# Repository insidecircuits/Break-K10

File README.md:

Break-K10
=========

Breakout board for Freescale Kinetis K10 QFN package - single sided PCB
![screenshot] (board scr.PNG)

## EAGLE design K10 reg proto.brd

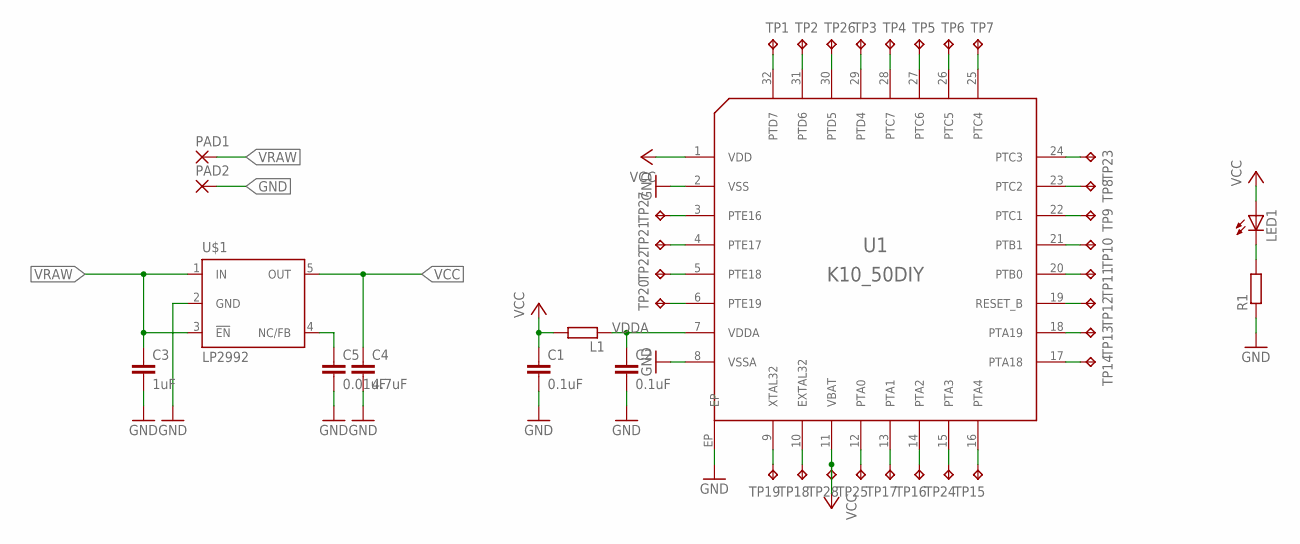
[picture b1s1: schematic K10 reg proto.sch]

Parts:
C1, C2: 0.1uF; C0805
C3: 1uF; C0805
C4: 4.7uF; C0805
C5: 0.01uF; C0805
L1: R-EU_R1206; R1206
LED1: LEDSML0805; SML0805
PAD1, PAD2: SMD2; SMD1,27-2,54
R1: R-EU_R0805; R0805
TP1, TP2, TP3, TP4, TP5, TP6, TP7, TP8, TP9, TP10, TP11, TP12, TP13, TP14, TP15, TP16, TP17, TP18, TP19, TP20, TP21, TP22, TP23, TP24, TP25, TP26, TP27, TP28: TPTP06R; TP06R
U1: K10_50DIY; QFN32-DIY
U$1: LP2992; SOT-23DBV

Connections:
3: TP27.TP, U1.3 (PTE16)
4: TP21.TP, U1.4 (PTE17)
6: TP20.TP, U1.6 (PTE19)
9: TP19.TP, U1.9 (XTAL32)
10: TP18.TP, U1.10 (EXTAL32)
12: TP25.TP, U1.12 (PTA0)
13: TP17.TP, U1.13 (PTA1)
14: TP16.TP, U1.14 (PTA2)
15: TP24.TP, U1.15 (PTA3)
16: TP15.TP, U1.16 (PTA4)
17: TP14.TP, U1.17 (PTA18)
18: TP13.TP, U1.18 (PTA19)
19: TP12.TP, U1.19 (RESET_B)
20: TP11.TP, U1.20 (PTB0)
21: TP10.TP, U1.21 (PTB1)
22: TP9.TP, U1.22 (PTC1)
23: TP8.TP, U1.23 (PTC2)
24: TP23.TP, U1.24 (PTC3)
25: TP7.TP, U1.25 (PTC4)
26: TP6.TP, U1.26 (PTC5)
27: TP5.TP, U1.27 (PTC6)
28: TP4.TP, U1.28 (PTC7)
29: TP3.TP, U1.29 (PTD4)
31: TP2.TP, U1.31 (PTD6)
32: TP1.TP, U1.32 (PTD7)
GND: C1.2, C2.2, C3.2, C4.2, C5.2, PAD2.1, R1.1, U1.2 (VSS), U1.8 (VSSA), U1.EP, U$1.2 (GND)
MIC: TP22.TP, U1.5 (PTE18)
unnamed: LED1.C, R1.2
unnamed: C5.1, U$1.4 (NC/FB)
unnamed: TP26.TP, U1.30 (PTD5)
VCC: C1.1, C4.1, L1.2, LED1.A, TP28.TP, U1.1 (VDD), U1.11 (VBAT), U$1.5 (OUT)
VDDA: C2.1, L1.1, U1.7 (VDDA)
VRAW: C3.1, PAD1.1, U$1.1 (IN), U$1.3 (!EN)

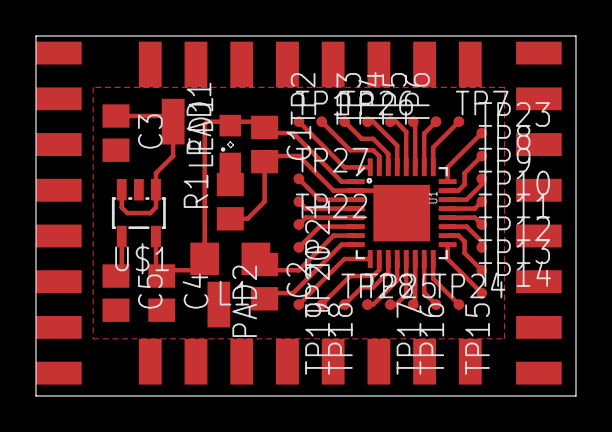
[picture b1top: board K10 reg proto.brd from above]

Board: 2 copper layers, 30.0 x 20.0 mm, 40 parts (0 on the bottom side), 33 nets.

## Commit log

2013-08-28 first stop
2013-08-28 something
2013-08-28 added files
2013-09-01 add screenshot in readme
